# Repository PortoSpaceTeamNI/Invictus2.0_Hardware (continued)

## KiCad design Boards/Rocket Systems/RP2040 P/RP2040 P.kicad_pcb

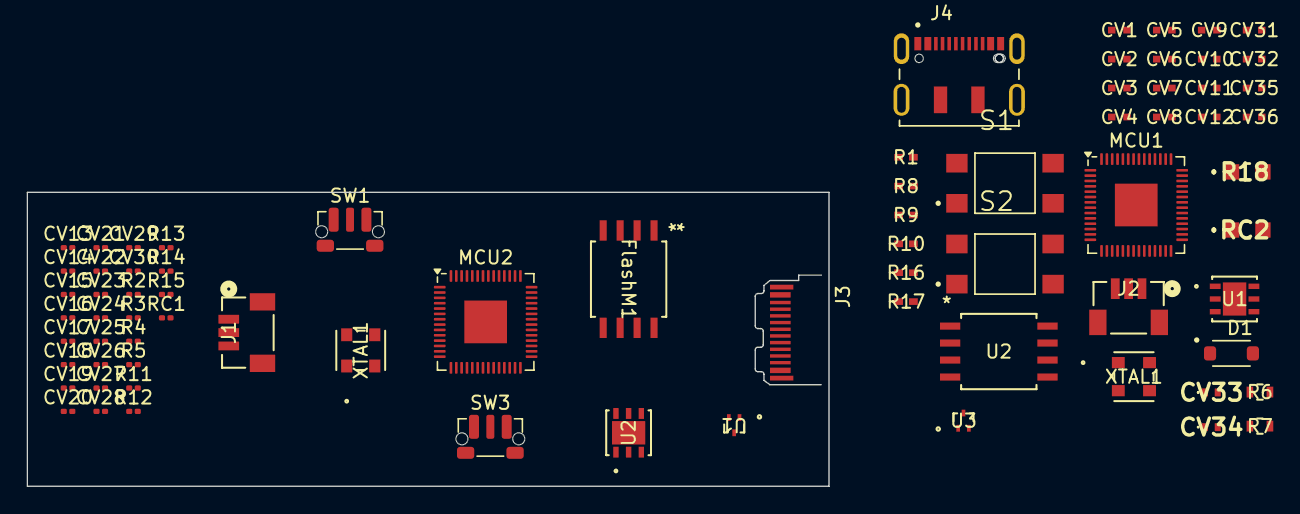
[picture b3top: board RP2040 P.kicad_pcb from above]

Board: 4 copper layers, 75 parts (0 on the bottom side), 47 nets, no tracks yet.

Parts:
CV1, CV3, CV6, CV31, CV35: 1uF; Capacitor_0402
CV2, CV4, CV5, CV7, CV8, CV9, CV10, CV11, CV12, CV32, CV36: 100nF; Capacitor_0402
CV13, CV15, CV18, CV25, CV29: 1uF; C_0201_0603Metric
CV14, CV16, CV17, CV19, CV20, CV21, CV22, CV23, CV24, CV26, CV30: 100nF; C_0201_0603Metric
CV27, CV28: 4.7uF; C_0201_0603Metric
CV33, CV34: 4.7uF; C_4uF7_0402
D1: PMEG2010ER; SODFL3517X110N
FlashM1: W25Q128JVSIQ_TR; SOIC_208MIL_WIN
J1, J2: BM03B-SRSS-TBLFSN; CONN_BM03B-SRSS-TBLFSN_JST
J3: USB_C; USB_C_Plug_JAE_DX07P024AJ1
J4: DX07S016JA1R1500; JAE_DX07S016JA1R1500
MCU1, MCU2: RP2040; QFN-56-1EP_7x7mm_P0.4mm_EP3.2x3.2mm
R1, R10, R17: 1k; RES_0402
R2, R12, R14: 1k; R_0201_0603Metric
R3, R4: 27; R_0201_0603Metric
R5, R11: 100; R_0201_0603Metric
R6, R7: 27; RES_R0603_27
R8, R9: 100; RES_0402
R13: 10k; R_0201_0603Metric
R15: 5k1; R_0201_0603Metric
R16: 10k; RES_0402
R18: 5k1; R_0805_5K1
RC1: 5k1; R_0201_0603Metric
RC2: 5k1; R_0805_5K1
S1, S2: TL3305CF160QG; SW_TL3305CF160QG
SW1, SW3: SW_Push; SW_Push_1P1T-MP_NO_Horizontal_Alps_SKRTLAE010
U1, U3: ESD7L5.0DT5G; SOT-723_0P85X1P25_ONS
U1#2, U2#2: ST1L05APU33R; DFN_5APU33R_STM
U2: W25Q128JVSIQ TR; SOIC_208MIL_WIN
XTAL1, XTAL1#2: ASE-12.000MHZ-LC-T; ASE-3.2X2.5_ABR

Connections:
+3.3V: CV5.1, CV6.1, CV7.1, CV8.1, CV9.1, CV10.1, CV11.1, CV12.1, CV17.1, CV18.1, CV19.1, CV20.1, CV21.1, CV22.1, CV23.1, CV24.1, CV25.1, CV26.1, CV28.2, CV30.1, CV31.1, CV32.1, CV34.2, CV36.1, FlashM1.8 (VCC), MCU1.1 (IOVDD), MCU1.10 (IOVDD), MCU1.22 (IOVDD), MCU1.33 (IOVDD), MCU1.42 (IOVDD), MCU1.43 (ADC_AVDD), MCU1.44 (VREG_IN), MCU1.48 (USB_VDD), MCU1.49 (IOVDD), MCU2.1 (IOVDD), MCU2.10 (IOVDD), MCU2.22 (IOVDD), MCU2.33 (IOVDD), MCU2.42 (IOVDD), MCU2.43 (ADC_AVDD), MCU2.44 (VREG_IN), MCU2.48 (USB_VDD), MCU2.49 (IOVDD), R1.1, R2.1, R13.2, R16.2, U1#2.2 (V0), U2.8 (VCC), U2#2.2 (V0), XTAL1.4 (VDD), XTAL1#2.4 (VDD)
/+5V: CV27.2, CV29.2, J3.A4 (VBUS), J3.A9 (VBUS), J3.B4 (VBUS), J3.B9 (VBUS), U2#2.3 (V1)
/MCU QSPI_SCLK: FlashM1.6 (CLK), MCU2.52 (QSPI_SCLK)
/MCU QSPI_SD0: FlashM1.5 (DI(IO0)), MCU2.53 (QSPI_SD0)
/MCU QSPI_SD1: FlashM1.2 (DO(IO1)), MCU2.55 (QSPI_SD1)
/MCU QSPI_SD2: FlashM1.3 (/WP(IO2)), MCU2.54 (QSPI_SD2)
/MCU QSPI_SD3: FlashM1.7 (/HOLD_/RESET), MCU2.51 (QSPI_SD3)
/MCU QSPI_SS: FlashM1.1 (/CS), MCU2.56 (QSPI_SS), R14.2
/RP2040 Standard/+5V: CV33.2, CV35.2, D1.C, U1#2.3 (V1)
/RP2040 Standard/MCU QSPI_SCLK: MCU1.52 (QSPI_SCLK), U2.6 (CLK)
/RP2040 Standard/MCU QSPI_SD0: MCU1.53 (QSPI_SD0), U2.5 (DI(IO0))
/RP2040 Standard/MCU QSPI_SD1: MCU1.55 (QSPI_SD1), U2.2 (DO(IO1))
/RP2040 Standard/MCU QSPI_SD2: MCU1.54 (QSPI_SD2), U2.3 (/WP(IO2))
/RP2040 Standard/MCU QSPI_SD3: MCU1.51 (QSPI_SD3), U2.7 (/HOLD_/RESET)
/RP2040 Standard/MCU QSPI_SS: MCU1.56 (QSPI_SS), R17.2, U2.1 (/CS)
/RP2040 Standard/USB_DM: J4.5 (D-), J4.8 (D-), R7.1, U3.1
/RP2040 Standard/USB_DP: J4.6 (D+), J4.7 (D+), R6.1, U3.2
/RP2040 Standard/~RST: R10.1, S2.4
/RP2040 Standard/~USB_BOOT: R17.1, S1.4
/USB_DM: J3.A7 (D-), J3.B7 (D-), R4.1, U1.1
/USB_DP: J3.A6 (D+), J3.B6 (D+), R3.1, U1.2
/~RST: R12.1, SW1.2
/~USB_BOOT: R14.1, SW3.2
CRYSTAL: MCU1.20 (XIN), MCU2.20 (XIN), XTAL1.3 (OUTPUT), XTAL1#2.3 (OUTPUT)
GND: CV1.2, CV2.1, CV3.2, CV4.1, CV5.2, CV6.2, CV7.2, CV8.2, CV9.2, CV10.2, CV11.2, CV12.2, CV13.2, CV14.1, CV15.2, CV16.1, CV17.2, CV18.2, CV19.2, CV20.2, CV21.2, CV22.2, CV23.2, CV24.2, CV25.2, CV26.2, CV27.1, CV28.1, CV29.1, CV30.2, CV31.2, CV32.2, CV33.1, CV34.1, CV35.1, CV36.2, FlashM1.4 (GND), J1.2, J2.2, J3.A1 (GND), J3.A12 (GND), J3.B1 (GND), J3.B12 (GND), J4.1 (GND), J4.12 (GND), MCU1.19 (TESTEN), MCU1.57 (GND), MCU2.19 (TESTEN), MCU2.57 (GND), R15.1, R18.1, RC1.1, RC2.1, S1.2, S2.2, SW1.1, SW3.1, U1.3, U1#2.6 (GND), U1#2.7 (GND), U2.4 (GND), U2#2.6 (GND), U2#2.7 (GND), U3.3, XTAL1.2 (GND/CASE), XTAL1#2.2 (GND/CASE)
unnamed: D1.A, J4.2 (VBUS), J4.11 (VBUS)
unnamed: J1.1, R5.1
unnamed: J1.3, R11.1
unnamed: J2.1, R9.1
unnamed: J2.3, R8.1
unnamed: J3.A5 (CC1), R15.2
unnamed: J3.B5 (CC2), RC1.2
unnamed: J4.3 (CC1), RC2.2
unnamed: J4.9 (CC2), R18.2
unnamed: CV1.1, MCU1.26 (RUN), R1.2, R10.2
unnamed: MCU1.24 (SWCLK), R8.2
unnamed: MCU1.25 (SWD), R9.2
unnamed: MCU1.46 (USB_DM), R7.2
unnamed: MCU1.47 (USB_DP), R6.2
unnamed: CV2.2, CV3.1, CV4.2, MCU1.23 (DVDD), MCU1.45 (VREG_VOUT), MCU1.50 (DVDD)
unnamed: CV13.1, MCU2.26 (RUN), R2.2, R12.2
unnamed: MCU2.24 (SWCLK), R5.2
unnamed: MCU2.25 (SWD), R11.2
unnamed: MCU2.46 (USB_DM), R4.2
unnamed: MCU2.47 (USB_DP), R3.2
unnamed: CV14.2, CV15.1, CV16.2, MCU2.23 (DVDD), MCU2.45 (VREG_VOUT), MCU2.50 (DVDD)
unnamed: R13.1, R16.1, XTAL1.1 (TRI-STATE(STBY)), XTAL1#2.1 (TRI-STATE(STBY))

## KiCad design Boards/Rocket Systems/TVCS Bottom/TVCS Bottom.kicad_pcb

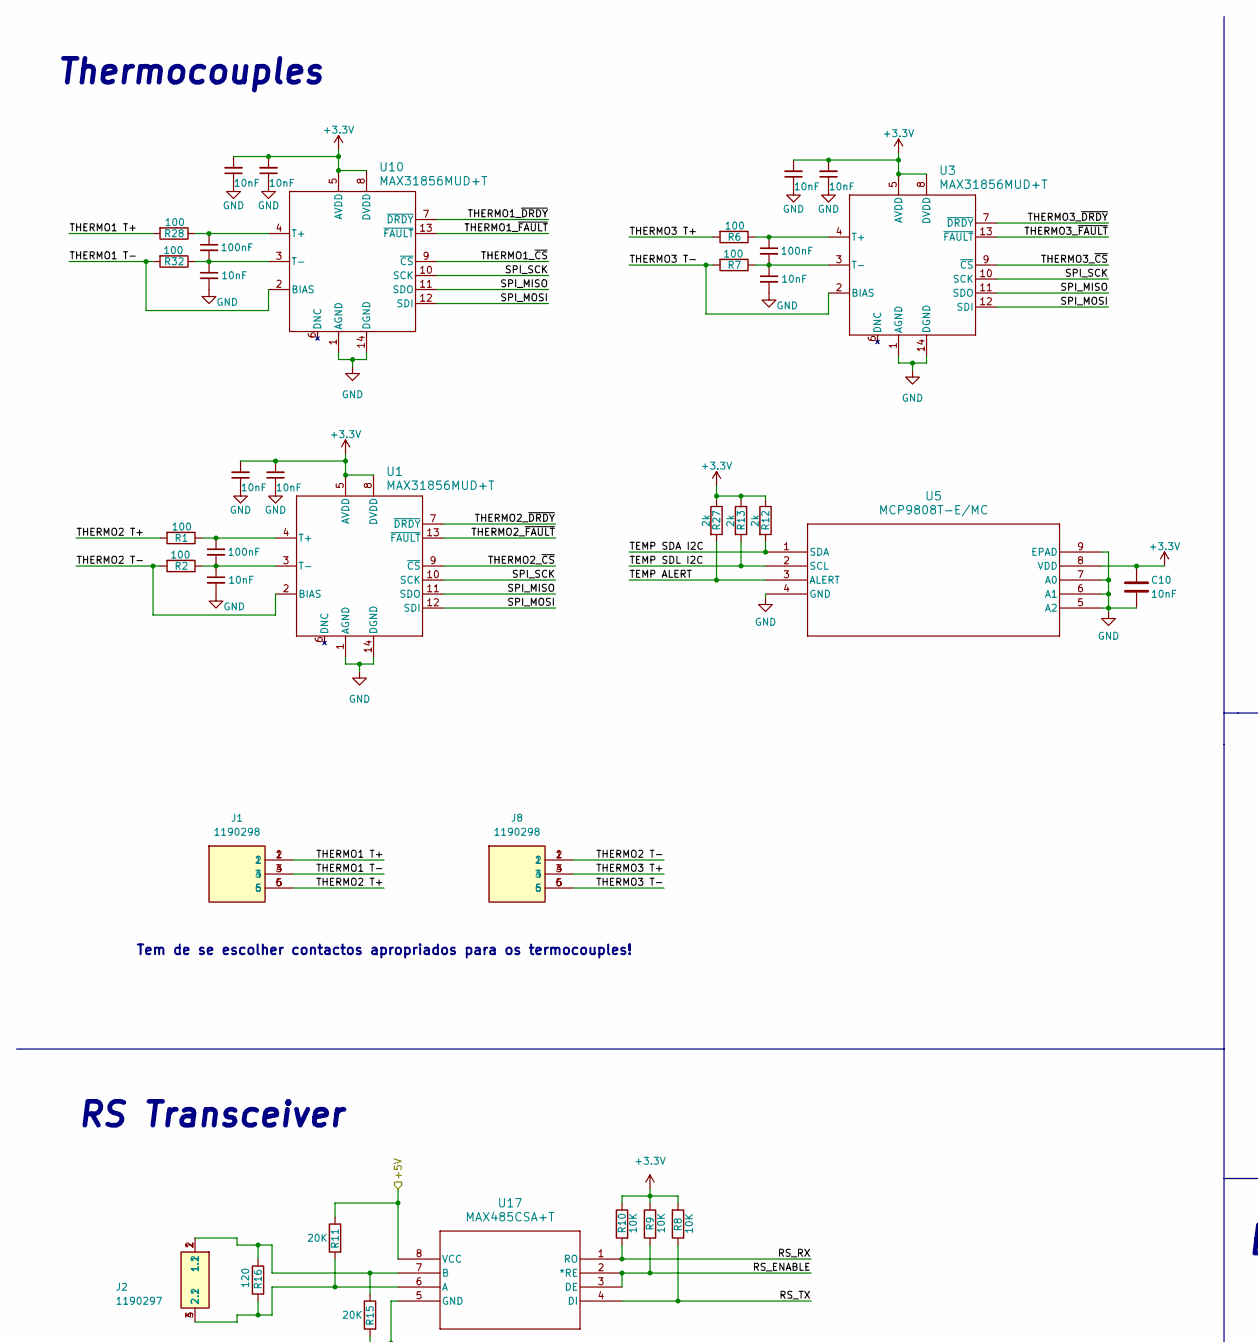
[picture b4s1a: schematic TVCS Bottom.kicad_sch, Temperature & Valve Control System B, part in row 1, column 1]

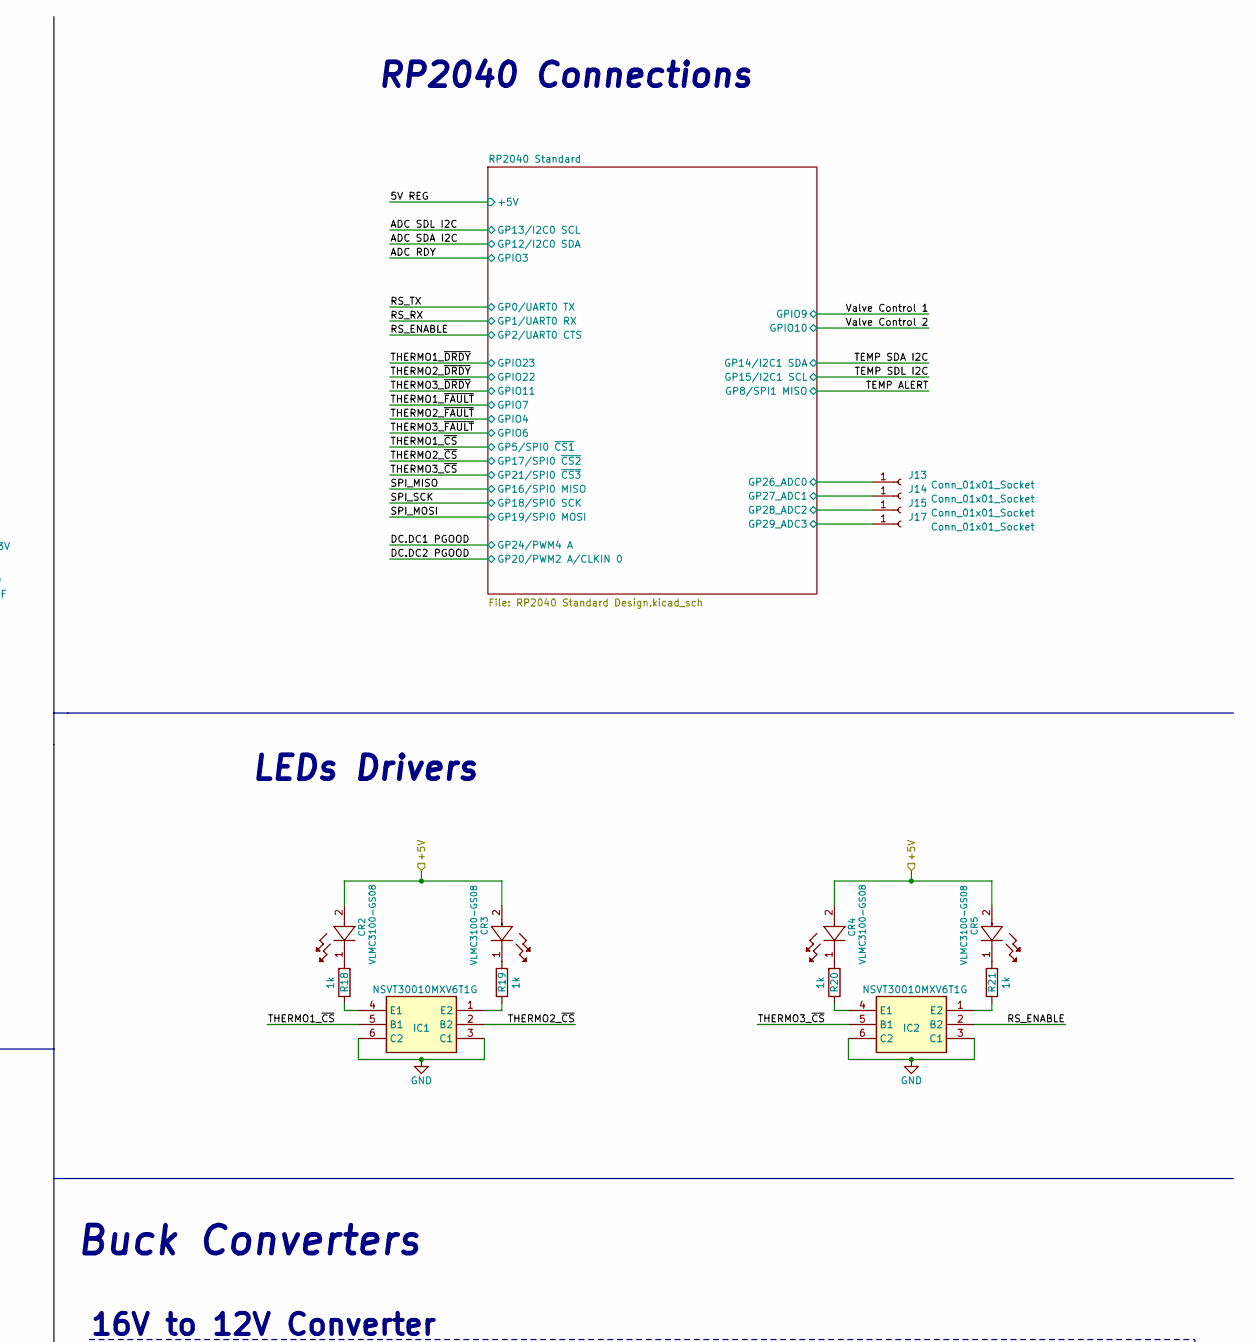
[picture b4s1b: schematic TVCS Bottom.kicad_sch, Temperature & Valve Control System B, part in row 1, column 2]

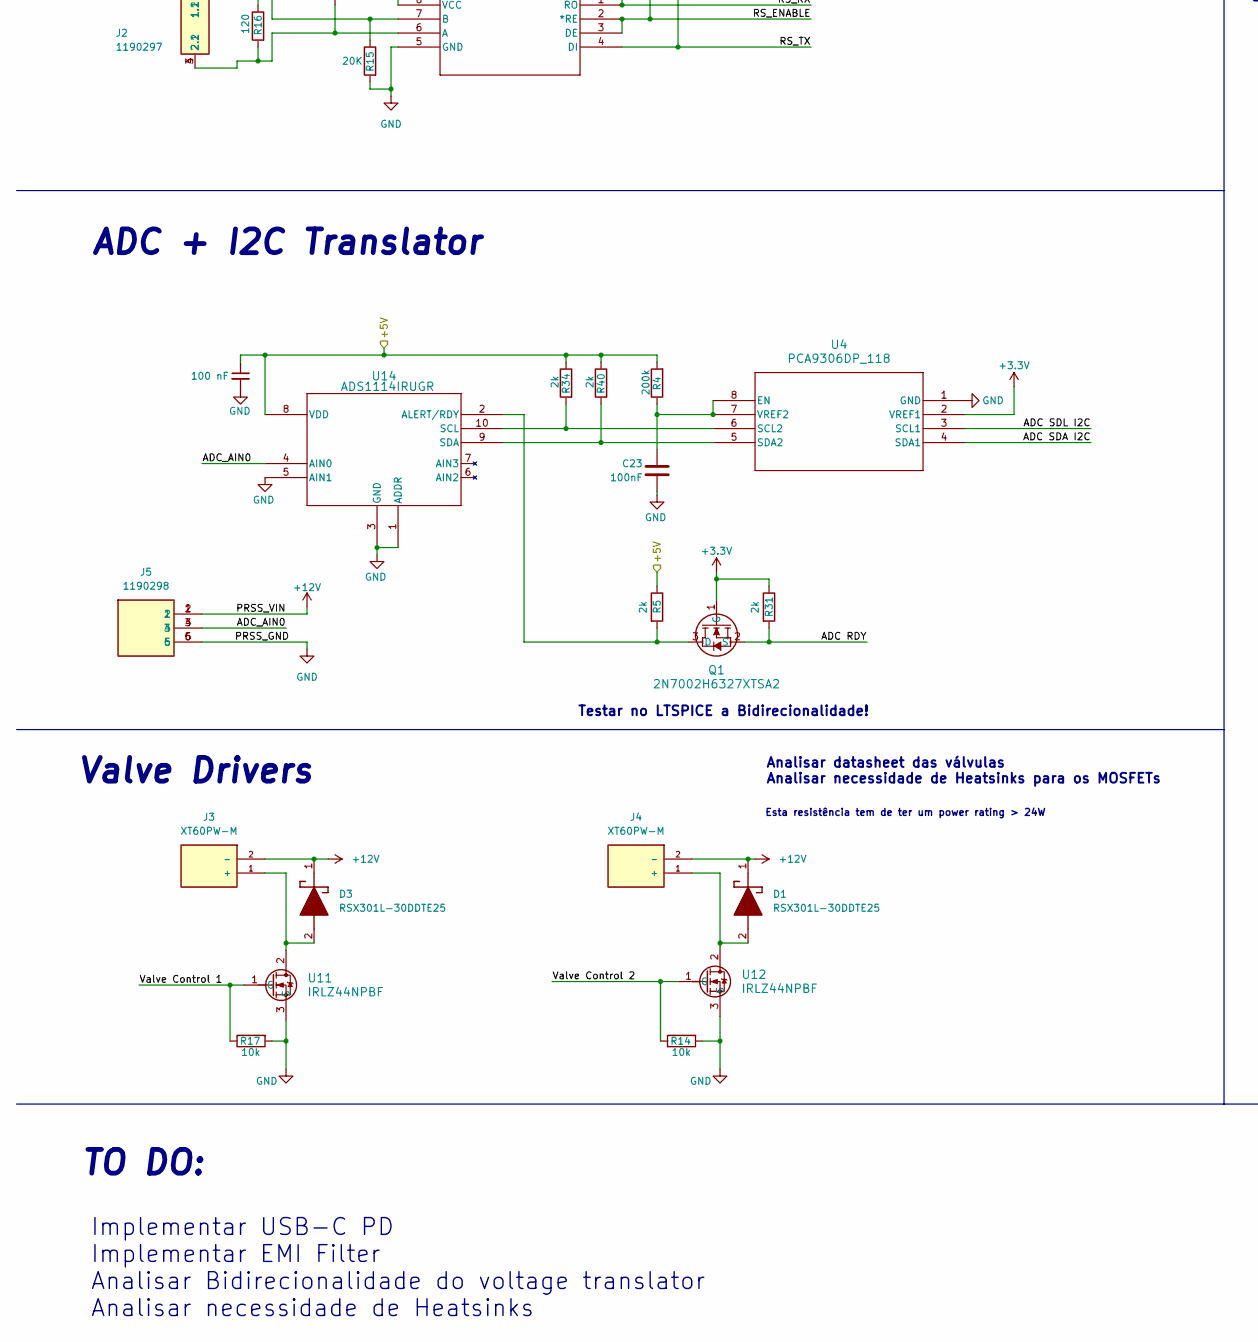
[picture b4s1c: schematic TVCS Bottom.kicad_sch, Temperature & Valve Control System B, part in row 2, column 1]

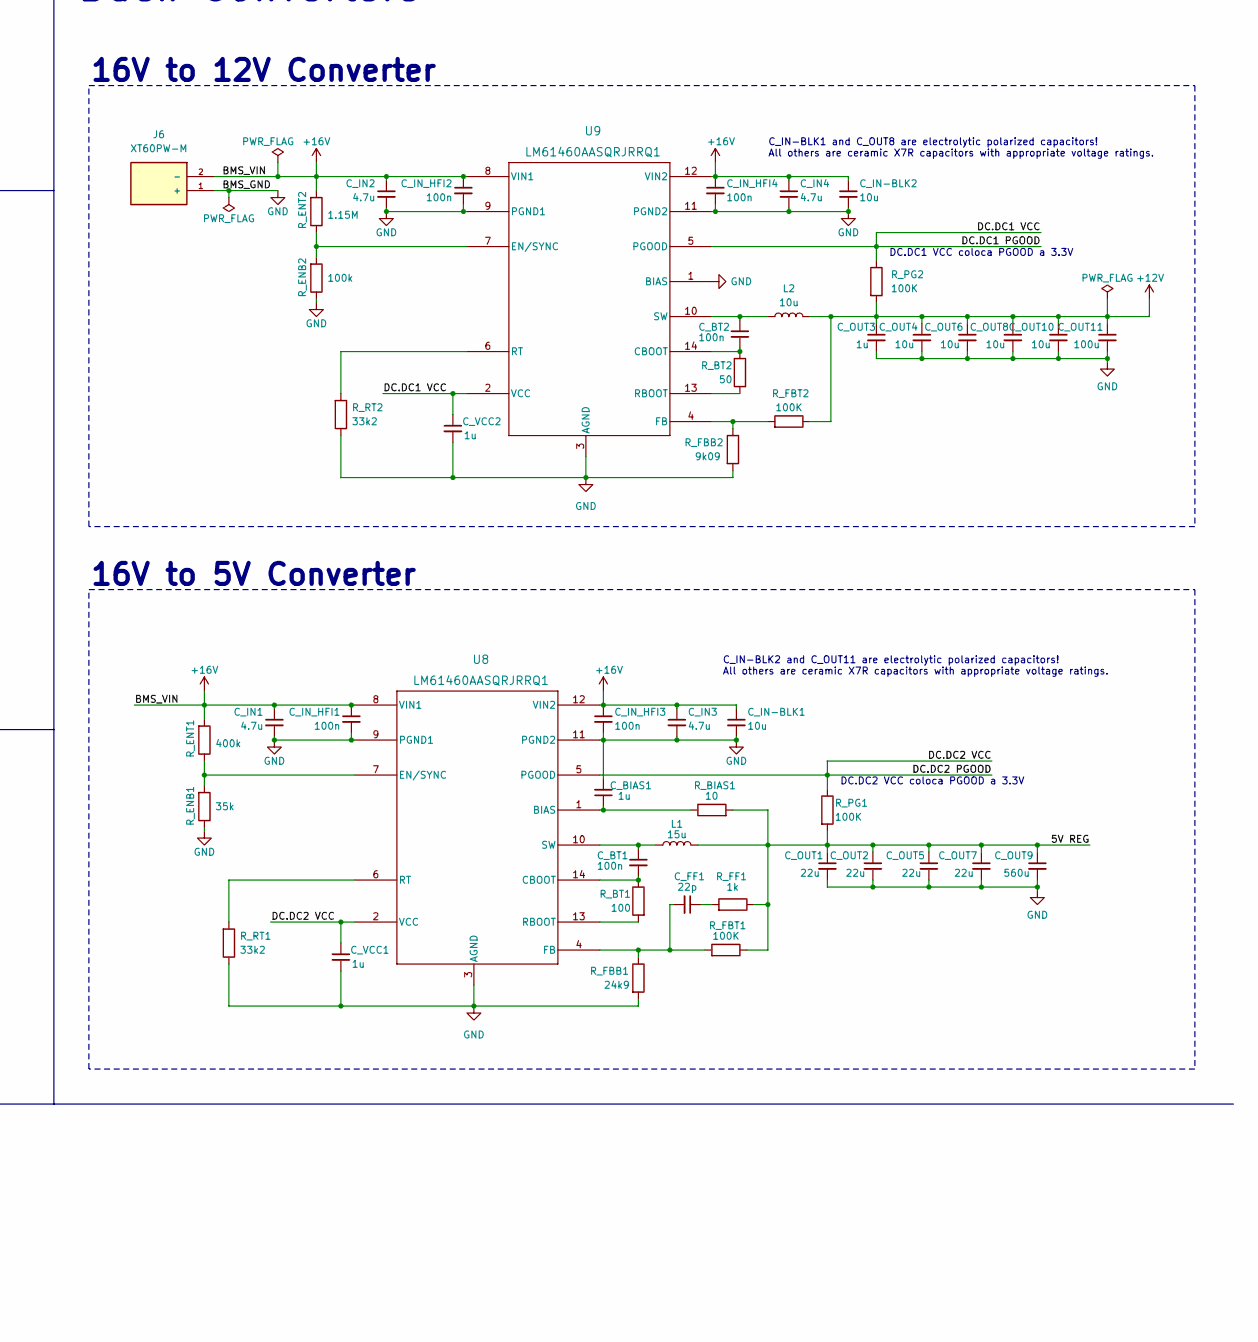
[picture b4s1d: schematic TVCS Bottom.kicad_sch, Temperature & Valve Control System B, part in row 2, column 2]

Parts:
C1, C6, C19, C23: 100nF; Capacitor_0402
C2, C3, C4, C7, C8, C9, C10, C17, C18, C20: 10nF; Capacitor_0402
C11: 100 nF; Capacitor_0402
CR2, CR3, CR4, CR5: VLMC3100-GS08; LED_PLCC_VSMB
C_BIAS1: 1u; Capacitor_0603
C_BT1, C_BT2: 100n; Capacitor_0402
C_FF1: 22p; Capacitor_0402
C_IN1, C_IN2, C_IN3, C_IN4: 4.7u; Capacitor_1206
C_IN-BLK1, C_IN-BLK2: 10u; Capacitor_4mm
C_IN_HFI1, C_IN_HFI2, C_IN_HFI3, C_IN_HFI4: 100n; Capacitor_0402
C_OUT1, C_OUT2, C_OUT5, C_OUT7: 22u; Capacitor_0805
C_OUT3: 1u; Capacitor_0603
C_OUT4, C_OUT6, C_OUT8, C_OUT10: 10u; Capacitor_0805
C_OUT9: 560u; Capacitor_8mm
C_OUT11: 100u; Capacitor_6mm
C_VCC1, C_VCC2: 1u; Capacitor_0603
D1, D3: RSX301L-30DDTE25; DIOM5026X220N; Mouser Part Number 755-RSX301L-30DDTE25
IC1, IC2: NSVT30010MXV6T1G; SOTFL50P160X60-6N; Mouser Part Number 863-NSVT30010MXV6T1G
J1, J5, J8: 1190298; Mouser Part Number 651-1190298
J2: 1190297; Mouser Part Number 651-1190297
J3, J4, J6: XT60PW-M; AMASS_XT60PW-M; PARTREV V1.2
J13, J14, J15, J17: Conn_01x01_Socket; Pico_01pin
L1: 15u; Inductor_10.1x10
L2: 10u; Inductor_11.5x10
Q1: 2N7002H6327XTSA2; PG-SOT23-3-5_INF_MIN
R1, R2, R6, R7, R28, R32: 100; RES_0402
R4: 200k; RES_0402
R5, R12, R13, R27, R31, R34, R40: 2k; RES_0402
R8, R9, R10: 10K; RES_0402
R11, R15: 20K; RES_0402
R14, R17: 10k; RES_0402
R16: 120; RES_0402
R18, R19, R20, R21: 1k; RES_0402
R_BIAS1: 10; RES_0402
R_BT1: 100; RES_0402
R_BT2: 50; RES_0402
R_ENB1: 35k; RES_0402
R_ENB2: 100k; RES_0603
R_ENT1: 400k; RES_0402
R_ENT2: 1.15M; RES_0603
R_FBB1: 24k9; RES_0603
R_FBB2: 9k09; RES_0603
R_FBT1, R_FBT2: 100K; RES_0603
R_FF1: 1k; RES_0402
R_PG1, R_PG2: 100K; RES_0603
R_RT1, R_RT2: 33k2; RES_0603
U1, U3, U10: MAX31856MUD+T; 21-0066J_14_MXM
U4: PCA9306DP_118; TSSOP8_SOT505-1_NXP
U5: MCP9808T-E/MC; DFN8_2x3MC_MCH
U8, U9: LM61460AASQRJRRQ1; VQFN-HR14_RJR_TEX
U11, U12: IRLZ44NPBF; PG-TO220-3_INF
U14: ADS1114IRUGR; ADS1114
U17: MAX485CSA+T; 21-0041-3-M_90-0096-8L_MXM

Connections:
+3.3V: C3.2, C4.2, C8.2, C9.2, C10.1, C17.2, C18.2, Q1.1 (G), R8.2, R9.1, R10.1, R12.1, R13.1, R27.1, R31.1, U1.5 (AVDD), U1.8 (DVDD), U3.5 (AVDD), U3.8 (DVDD), U4.2 (VREF1), U5.8 (VDD), U10.5 (AVDD), U10.8 (DVDD); also elsewhere on the board
+5V: C11.1, CR2.2, CR3.2, CR4.2, CR5.2, R4.2, R5.1, R11.1, R34.1, R40.1, U14.8 (VDD), U17.8 (VCC)
+12V: C_OUT3.1, C_OUT4.1, C_OUT6.1, C_OUT8.1, C_OUT10.1, C_OUT11.1, D1.1 (K), D3.1 (K), J3.2 (-), J4.2 (-), J5.1, J5.2, L2.2, R_FBT2.1, R_PG2.2
+16V: C_IN1.1, C_IN2.1, C_IN3.1, C_IN4.1, C_IN-BLK1.1, C_IN-BLK2.1, C_IN_HFI1.1, C_IN_HFI2.1, C_IN_HFI3.1, C_IN_HFI4.1, J6.2 (-), R_ENT1.2, R_ENT2.2, U8.8 (VIN1), U8.12 (VIN2), U9.8 (VIN1), U9.12 (VIN2)
/5V REG: C_OUT1.1, C_OUT2.1, C_OUT5.1, C_OUT7.1, C_OUT9.1, L1.2, R_BIAS1.2, R_FBT1.1, R_FF1.1, R_PG1.2; also elsewhere on the board
/ADC RDY: Q1.2 (S), R31.2; also elsewhere on the board
/ADC SDA I2C: U4.4 (SDA1); also elsewhere on the board
/ADC SDL I2C: U4.3 (SCL1); also elsewhere on the board
/ADC_AIN0: J5.3, J5.4, U14.4 (AIN0)
/DC.DC1 PGOOD: C_VCC2.1, R_PG2.1, U9.2 (VCC), U9.5 (PGOOD); also elsewhere on the board
/DC.DC2 PGOOD: C_VCC1.1, R_PG1.1, U8.2 (VCC), U8.5 (PGOOD); also elsewhere on the board
/RP2040 Standard/GP26_ADC0: J13.1; also elsewhere on the board
/RP2040 Standard/GP27_ADC1: J14.1; also elsewhere on the board
/RP2040 Standard/GP28_ADC2: J15.1; also elsewhere on the board
/RP2040 Standard/GP29_ADC3: J17.1; also elsewhere on the board
/RS_ENABLE: IC2.2 (B2), R9.2, U17.2 (*RE), U17.3 (DE); also elsewhere on the board
/RS_RX: R10.2, U17.1 (RO); also elsewhere on the board
/RS_TX: R8.1, U17.4 (DI); also elsewhere on the board
/SPI_MISO: U1.11 (SDO), U3.11 (SDO), U10.11 (SDO); also elsewhere on the board
/SPI_MOSI: U1.12 (SDI), U3.12 (SDI), U10.12 (SDI); also elsewhere on the board
/SPI_SCK: U1.10 (SCK), U3.10 (SCK), U10.10 (SCK); also elsewhere on the board
/TEMP ALERT: R27.2, U5.3 (ALERT); also elsewhere on the board
/TEMP SDA I2C: R12.2, U5.1 (SDA); also elsewhere on the board
/TEMP SDL I2C: R13.2, U5.2 (SCL); also elsewhere on the board
/THERMO1 T+: J1.1, J1.2, R28.2
/THERMO1 T-: J1.3, J1.4, R32.2, U10.2 (BIAS)
/THERMO1_~CS: IC1.5 (B1), U10.9 (~CS); also elsewhere on the board
/THERMO1_~DRDY: U10.7 (~DRDY); also elsewhere on the board
/THERMO1_~FAULT: U10.13 (~FAULT); also elsewhere on the board
/THERMO2 T+: J1.5, J1.6, R1.2
/THERMO2 T-: J8.1, J8.2, R2.2, U1.2 (BIAS)
/THERMO2_~CS: IC1.2 (B2), U1.9 (~CS); also elsewhere on the board
/THERMO2_~DRDY: U1.7 (~DRDY); also elsewhere on the board
/THERMO2_~FAULT: U1.13 (~FAULT); also elsewhere on the board
/THERMO3 T+: J8.3, J8.4, R6.2
/THERMO3 T-: J8.5, J8.6, R7.2, U3.2 (BIAS)
/THERMO3_~CS: IC2.5 (B1), U3.9 (~CS); also elsewhere on the board
/THERMO3_~DRDY: U3.7 (~DRDY); also elsewhere on the board
/THERMO3_~FAULT: U3.13 (~FAULT); also elsewhere on the board
/Valve Control 1: R17.1, U11.1 (G); also elsewhere on the board
/Valve Control 2: R14.1, U12.1 (G); also elsewhere on the board
GND: C2.2, C3.1, C4.1, C7.2, C8.1, C9.1, C10.2, C11.2, C17.1, C18.1, C20.2, C23.2, C_BIAS1.2, C_IN1.2, C_IN2.2, C_IN3.2, C_IN4.2, C_IN-BLK1.2, C_IN-BLK2.2, C_IN_HFI1.2, C_IN_HFI2.2, C_IN_HFI3.2, C_IN_HFI4.2, C_OUT1.2, C_OUT2.2, C_OUT3.2, C_OUT4.2, C_OUT5.2, C_OUT6.2, C_OUT7.2, C_OUT8.2, C_OUT9.2, C_OUT10.2, C_OUT11.2, C_VCC1.2, C_VCC2.2, IC1.3 (C1), IC1.6 (C2), IC2.3 (C1), IC2.6 (C2), J5.5, J5.6, J6.1 (+), R14.2, R15.2, R17.2, R_ENB1.1, R_ENB2.1, R_FBB1.2, R_FBB2.2, R_RT1.1, R_RT2.1, U1.1 (AGND), U1.14 (DGND), U3.1 (AGND), U3.14 (DGND), U4.1 (GND), U5.4 (GND), U5.5 (A2), U5.6 (A1), U5.7 (A0), U5.9 (EPAD), U8.3 (AGND), U8.9 (PGND1), U8.11 (PGND2), U9.1 (BIAS), U9.3 (AGND), U9.9 (PGND1), U9.11 (PGND2), U10.1 (AGND), U10.14 (DGND), U11.3 (S), U12.3 (S), U14.1 (ADDR), U14.3 (GND), U14.5 (AIN1), U17.5 (GND); also elsewhere on the board
unnamed: CR2.1, R18.2
unnamed: CR3.1, R19.2
unnamed: CR4.1, R20.2
unnamed: CR5.1, R21.2
unnamed: C_FF1.1, R_FF1.2
unnamed: D1.2 (A), J4.1 (+), U12.2
unnamed: D3.2 (A), J3.1 (+), U11.2
unnamed: IC1.4 (E1), R18.1
unnamed: IC1.1 (E2), R19.1
unnamed: IC2.4 (E1), R20.1
unnamed: IC2.1 (E2), R21.1
unnamed: J2.1 (1.1), J2.2 (1.2), R15.1, R16.1, U17.7 (B)
unnamed: J2.3 (2.1), J2.4 (2.2), R11.2, R16.2, U17.6 (A)
unnamed: Q1.3 (D), R5.2, U14.2 (ALERT/RDY)
unnamed: C1.1, R1.1, U1.4 (T+)
unnamed: C1.2, C2.1, R2.1, U1.3 (T-)
unnamed: C6.1, R6.1, U3.4 (T+)
unnamed: C6.2, C7.1, R7.1, U3.3 (T-)
unnamed: C23.1, R4.1, U4.7 (VREF2), U4.8 (EN)
unnamed: C_BIAS1.1, R_BIAS1.1, U8.1 (BIAS)
unnamed: C_BT1.2, R_BT1.1, U8.14 (CBOOT)
unnamed: R_ENB1.2, R_ENT1.1, U8.7 (EN/SYNC)
unnamed: C_FF1.2, R_FBB1.1, R_FBT1.2, U8.4 (FB)
unnamed: R_BT1.2, U8.13 (RBOOT)
unnamed: R_RT1.2, U8.6 (RT)
unnamed: C_BT1.1, L1.1, U8.10 (SW)
unnamed: C_BT2.2, R_BT2.1, U9.14 (CBOOT)
unnamed: R_ENB2.2, R_ENT2.1, U9.7 (EN/SYNC)
unnamed: R_FBB2.1, R_FBT2.2, U9.4 (FB)
unnamed: R_BT2.2, U9.13 (RBOOT)
unnamed: R_RT2.2, U9.6 (RT)
unnamed: C_BT2.1, L2.1, U9.10 (SW)
unnamed: C19.1, R28.1, U10.4 (T+)
unnamed: C19.2, C20.1, R32.1, U10.3 (T-)
unnamed: R34.2, U4.6 (SCL2), U14.10 (SCL)
unnamed: R40.2, U4.5 (SDA2), U14.9 (SDA)

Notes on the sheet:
Testar no LTSPICE a Bidirecionalidade!
Buck Converters
RP2040 Connections
TO DO:
16V to 12V Converter
Valve Drivers
Esta resistência tem de ter um power rating > 24W
LEDs Drivers
Analisar datasheet das válvulas Analisar necessidade de Heatsinks para os MOSFETs
Thermocouples
Implementar USB-C PD Implementar EMI Filter Analisar Bidirecionalidade do voltage translator Analisar necessidade de Heatsinks
C_IN-BLK2 and C_OUT11 are electrolytic polarized capacitors! All others are ceramic X7R capacitors with appropriate voltage ratings.
16V to 5V Converter
C_IN-BLK1 and C_OUT8 are electrolytic polarized capacitors! All others are ceramic X7R capacitors with appropriate voltage ratings.
DC.DC1 VCC coloca PGOOD a 3.3V
RS Transceiver
Tem de se escolher contactos apropriados para os termocouples!
ADC + I2C Translator
DC.DC2 VCC coloca PGOOD a 3.3V

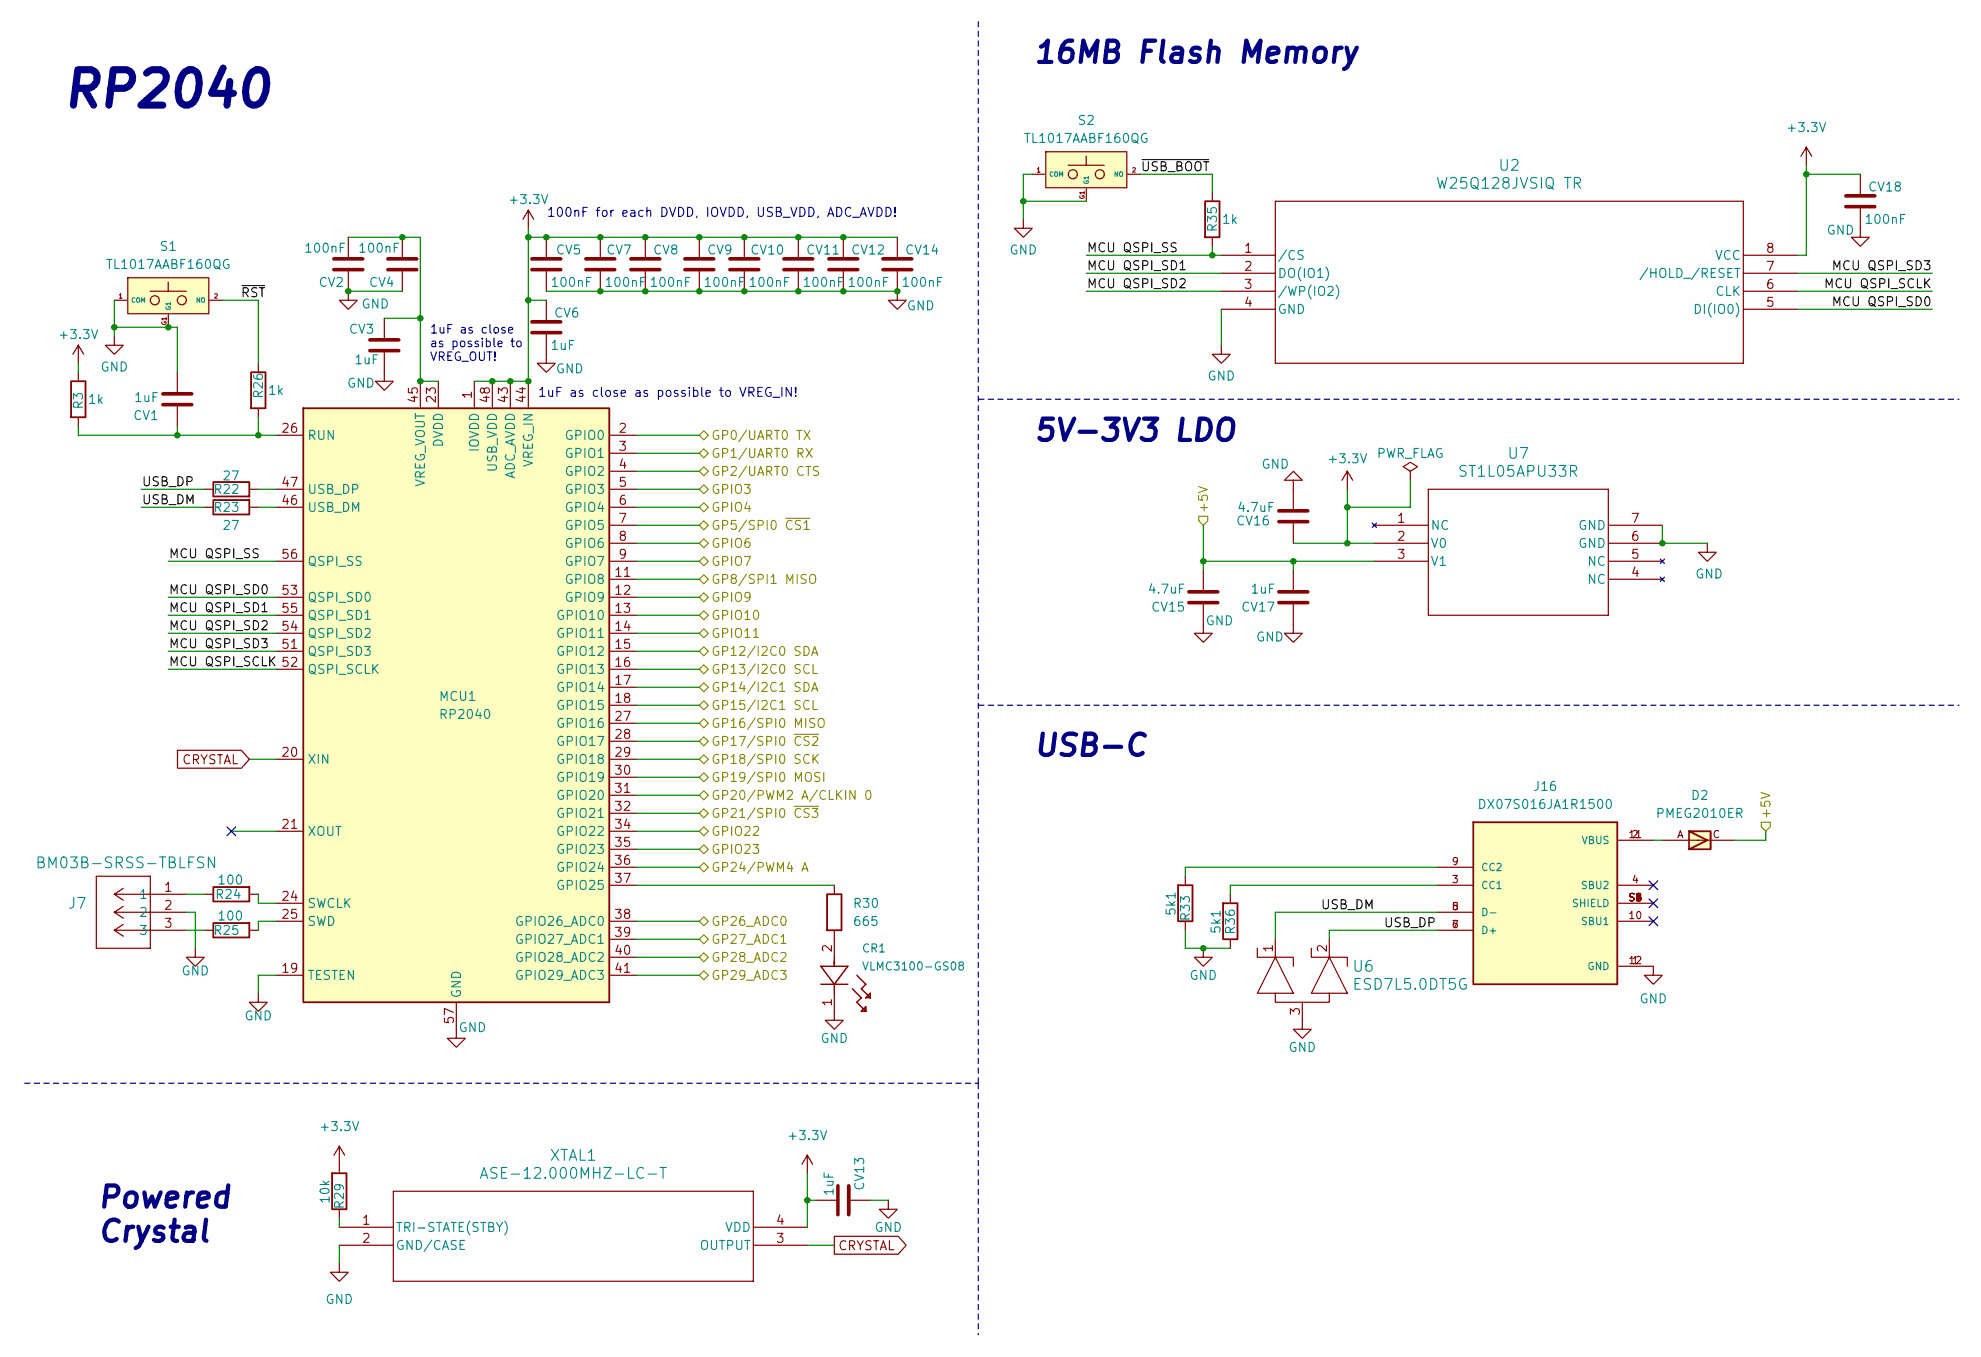
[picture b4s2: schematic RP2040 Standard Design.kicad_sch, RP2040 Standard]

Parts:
CR1: VLMC3100-GS08; LED_PLCC_VSMB
CV1, CV3, CV6, CV13, CV17: 1uF; Capacitor_0402
CV2, CV4, CV5, CV7, CV8, CV9, CV10, CV11, CV12, CV14, CV18: 100nF; Capacitor_0402
CV15, CV16: 4.7uF; Capacitor_0402
D2: PMEG2010ER; SODFL3517X110N; PARTREV 01
J7: BM03B-SRSS-TBLFSN; CONN_BM03B-SRSS-TBLFSN_JST
J16: DX07S016JA1R1500; JAE_DX07S016JA1R1500; PARTREV 1
MCU1: RP2040; QFN-56-1EP_7x7mm_P0.4mm_EP3.2x3.2mm
R3, R26, R35: 1k; RES_0402
R22, R23: 27; RES_0603
R24, R25: 100; RES_0402
R29: 10k; RES_0402
R30: 665; RES_0402
R33, R36: 5k1; RES_0805
S1, S2: TL1017AABF160QG; Mouser Part Number 612-TL1017AABF160QG
U2: W25Q128JVSIQ TR; SOIC_208MIL_WIN
U6: ESD7L5.0DT5G; SOT-723_0P85X1P25_ONS
U7: ST1L05APU33R; DFN_5APU33R_STM
XTAL1: ASE-12.000MHZ-LC-T; ASE-3.2X2.5_ABR

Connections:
+3.3V: CV5.1, CV6.1, CV7.1, CV8.1, CV9.1, CV10.1, CV11.1, CV12.1, CV13.1, CV14.1, CV16.2, CV18.1, MCU1.1 (IOVDD), MCU1.10 (IOVDD), MCU1.22 (IOVDD), MCU1.33 (IOVDD), MCU1.42 (IOVDD), MCU1.43 (ADC_AVDD), MCU1.44 (VREG_IN), MCU1.48 (USB_VDD), MCU1.49 (IOVDD), R3.1, R29.2, U2.8 (VCC), U7.2 (V0), XTAL1.4 (VDD); also elsewhere on the board
/5V REG: CV15.2, CV17.2, D2.C, U7.3 (V1); also elsewhere on the board
/ADC RDY: MCU1.5 (GPIO3); also elsewhere on the board
/ADC SDA I2C: MCU1.15 (GPIO12); also elsewhere on the board
/ADC SDL I2C: MCU1.16 (GPIO13); also elsewhere on the board
/DC.DC1 PGOOD: MCU1.36 (GPIO24); also elsewhere on the board
/DC.DC2 PGOOD: MCU1.31 (GPIO20); also elsewhere on the board
/RP2040 Standard/GP26_ADC0: MCU1.38 (GPIO26_ADC0); also elsewhere on the board
/RP2040 Standard/GP27_ADC1: MCU1.39 (GPIO27_ADC1); also elsewhere on the board
/RP2040 Standard/GP28_ADC2: MCU1.40 (GPIO28_ADC2); also elsewhere on the board
/RP2040 Standard/GP29_ADC3: MCU1.41 (GPIO29_ADC3); also elsewhere on the board
/RP2040 Standard/MCU QSPI_SCLK: MCU1.52 (QSPI_SCLK), U2.6 (CLK)
/RP2040 Standard/MCU QSPI_SD0: MCU1.53 (QSPI_SD0), U2.5 (DI(IO0))
/RP2040 Standard/MCU QSPI_SD1: MCU1.55 (QSPI_SD1), U2.2 (DO(IO1))
/RP2040 Standard/MCU QSPI_SD2: MCU1.54 (QSPI_SD2), U2.3 (/WP(IO2))
/RP2040 Standard/MCU QSPI_SD3: MCU1.51 (QSPI_SD3), U2.7 (/HOLD_/RESET)
/RP2040 Standard/MCU QSPI_SS: MCU1.56 (QSPI_SS), R35.2, U2.1 (/CS)
/RP2040 Standard/USB_DM: J16.5 (D-), J16.8 (D-), R23.1, U6.1
/RP2040 Standard/USB_DP: J16.6 (D+), J16.7 (D+), R22.1, U6.2
/RP2040 Standard/~RST: R26.1, S1.2 (NO)
/RP2040 Standard/~USB_BOOT: R35.1, S2.2 (NO)
/RS_ENABLE: MCU1.4 (GPIO2); also elsewhere on the board
/RS_RX: MCU1.3 (GPIO1); also elsewhere on the board
/RS_TX: MCU1.2 (GPIO0); also elsewhere on the board
/SPI_MISO: MCU1.27 (GPIO16); also elsewhere on the board
/SPI_MOSI: MCU1.30 (GPIO19); also elsewhere on the board
/SPI_SCK: MCU1.29 (GPIO18); also elsewhere on the board
/TEMP ALERT: MCU1.11 (GPIO8); also elsewhere on the board
/TEMP SDA I2C: MCU1.17 (GPIO14); also elsewhere on the board
/TEMP SDL I2C: MCU1.18 (GPIO15); also elsewhere on the board
/THERMO1_~CS: MCU1.7 (GPIO5); also elsewhere on the board
/THERMO1_~DRDY: MCU1.35 (GPIO23); also elsewhere on the board
/THERMO1_~FAULT: MCU1.9 (GPIO7); also elsewhere on the board
/THERMO2_~CS: MCU1.28 (GPIO17); also elsewhere on the board
/THERMO2_~DRDY: MCU1.34 (GPIO22); also elsewhere on the board
/THERMO2_~FAULT: MCU1.6 (GPIO4); also elsewhere on the board
/THERMO3_~CS: MCU1.32 (GPIO21); also elsewhere on the board
/THERMO3_~DRDY: MCU1.14 (GPIO11); also elsewhere on the board
/THERMO3_~FAULT: MCU1.8 (GPIO6); also elsewhere on the board
/Valve Control 1: MCU1.12 (GPIO9); also elsewhere on the board
/Valve Control 2: MCU1.13 (GPIO10); also elsewhere on the board
CRYSTAL: MCU1.20 (XIN), XTAL1.3 (OUTPUT)
GND: CR1.1, CV1.2, CV2.1, CV3.2, CV4.1, CV5.2, CV6.2, CV7.2, CV8.2, CV9.2, CV10.2, CV11.2, CV12.2, CV13.2, CV14.2, CV15.1, CV16.1, CV17.1, CV18.2, J7.2, J16.1 (GND), J16.12 (GND), MCU1.19 (TESTEN), MCU1.57 (GND), R33.1, R36.1, S1.1 (COM), S1.G1, S2.1 (COM), S2.G1, U2.4 (GND), U6.3, U7.6 (GND), U7.7 (GND), XTAL1.2 (GND/CASE); also elsewhere on the board
unnamed: CR1.2, R30.2
unnamed: D2.A, J16.2 (VBUS), J16.11 (VBUS)
unnamed: J7.1, R24.1
unnamed: J7.3, R25.1
unnamed: J16.3 (CC1), R36.2
unnamed: J16.9 (CC2), R33.2
unnamed: MCU1.37 (GPIO25), R30.1
unnamed: CV1.1, MCU1.26 (RUN), R3.2, R26.2
unnamed: MCU1.24 (SWCLK), R24.2
unnamed: MCU1.25 (SWD), R25.2
unnamed: MCU1.46 (USB_DM), R23.2
unnamed: MCU1.47 (USB_DP), R22.2
unnamed: CV2.2, CV3.1, CV4.2, MCU1.23 (DVDD), MCU1.45 (VREG_VOUT), MCU1.50 (DVDD)
unnamed: R29.1, XTAL1.1 (TRI-STATE(STBY))

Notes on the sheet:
Powered Crystal
16MB Flash Memory
100nF for each DVDD, IOVDD, USB_VDD, ADC_AVDD!
1uF as close as possible to VREG_OUT!
5V-3V3 LDO
1uF as close as possible to VREG_IN!
RP2040
USB-C

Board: 6 copper layers, 157 parts (0 on the bottom side), 103 nets, no tracks yet.
